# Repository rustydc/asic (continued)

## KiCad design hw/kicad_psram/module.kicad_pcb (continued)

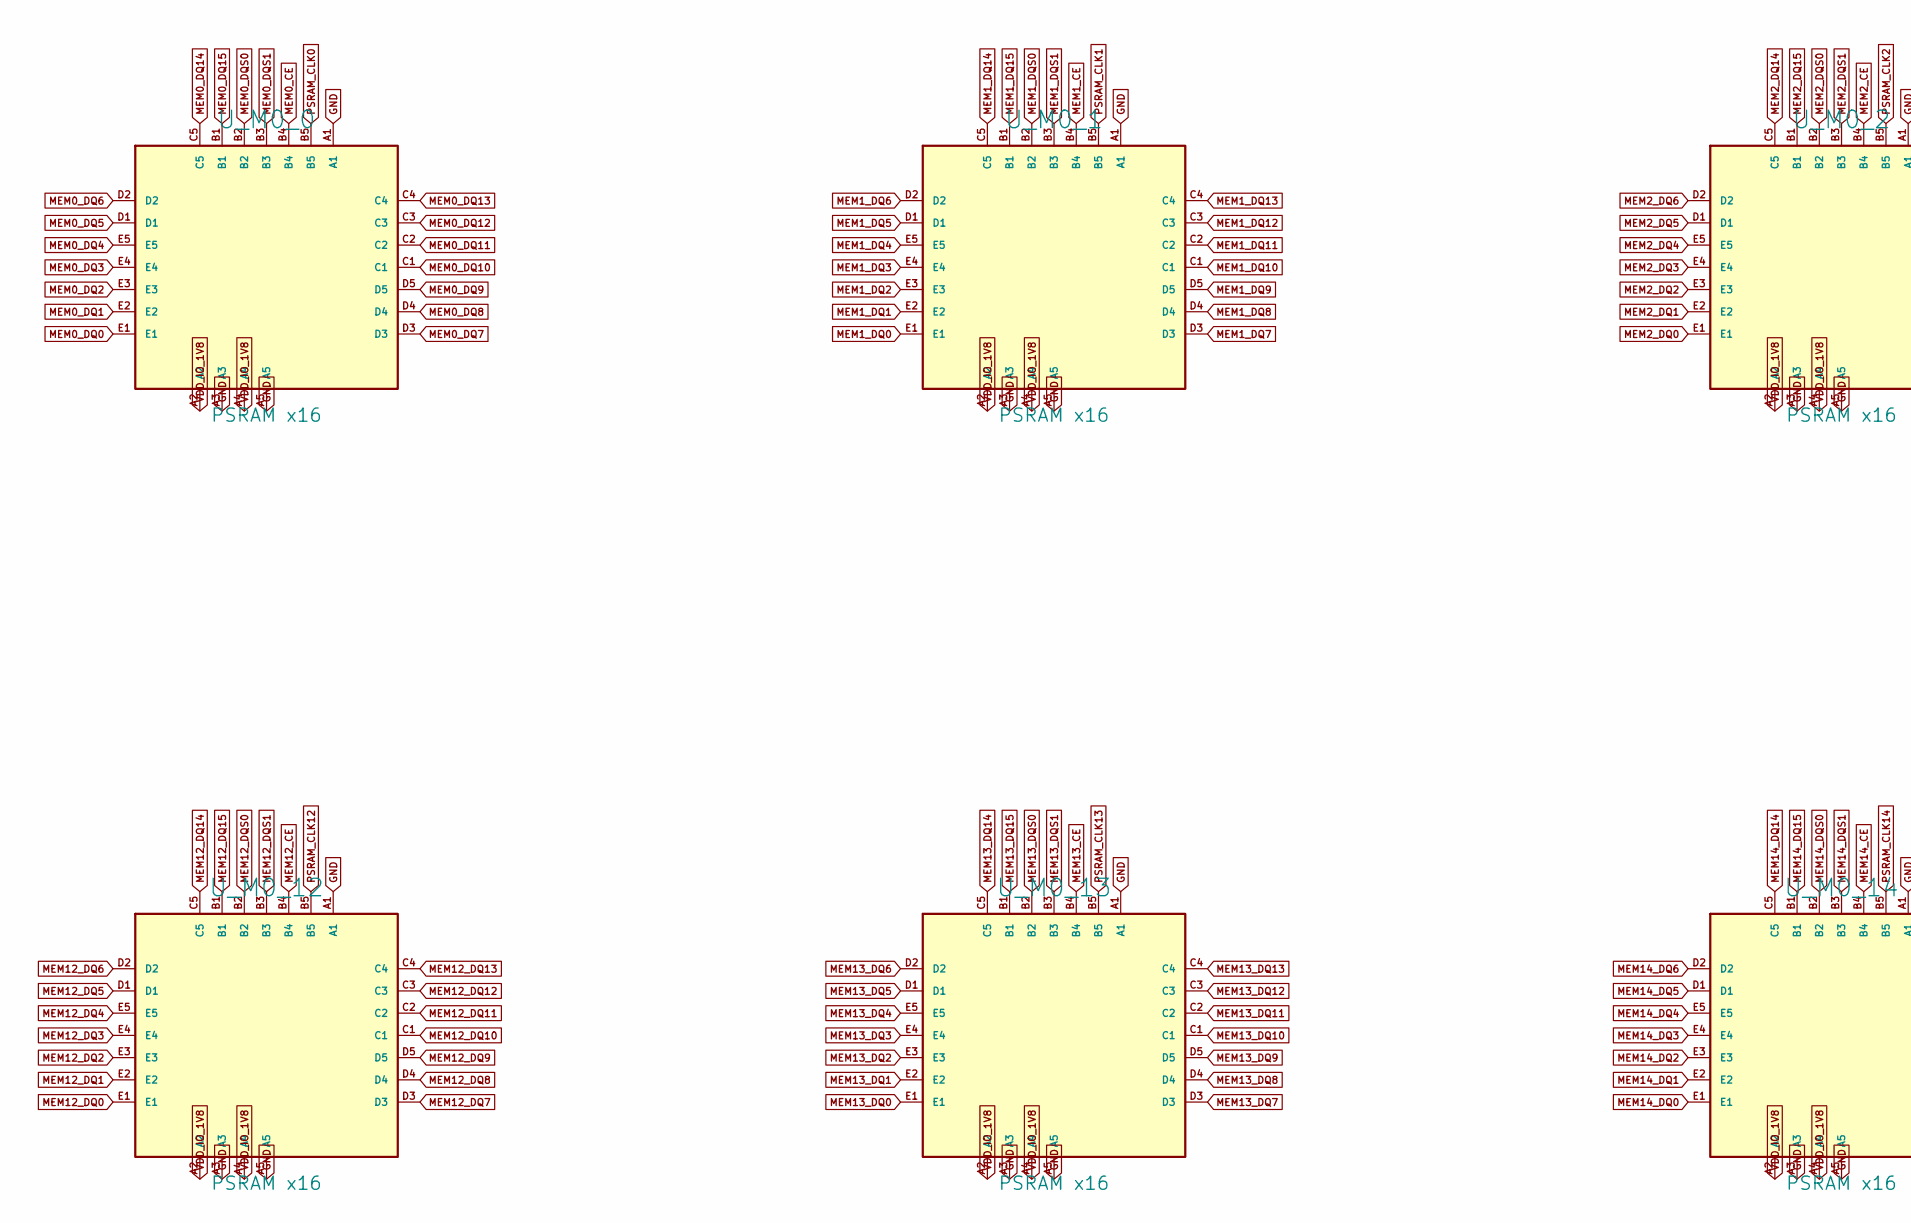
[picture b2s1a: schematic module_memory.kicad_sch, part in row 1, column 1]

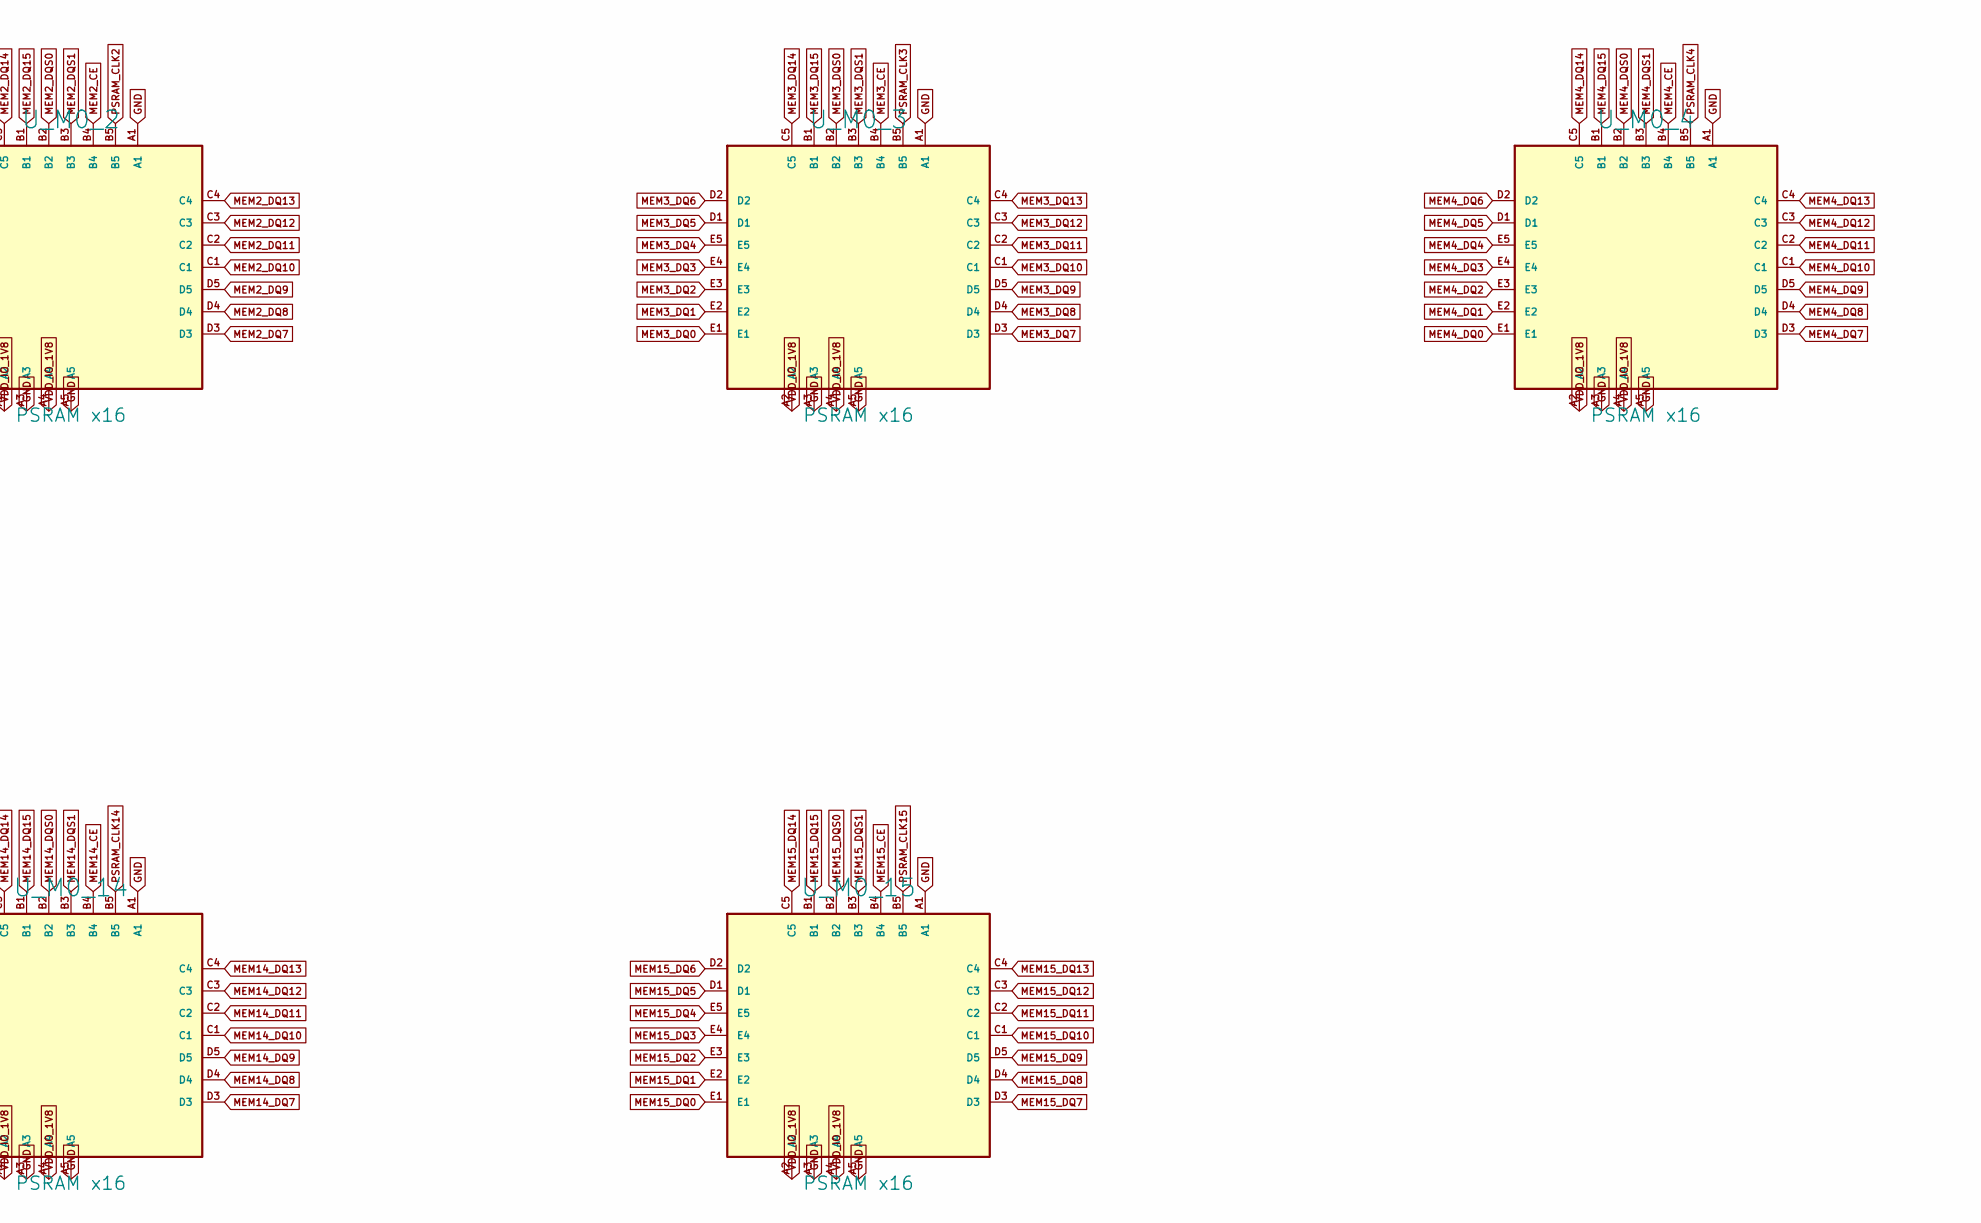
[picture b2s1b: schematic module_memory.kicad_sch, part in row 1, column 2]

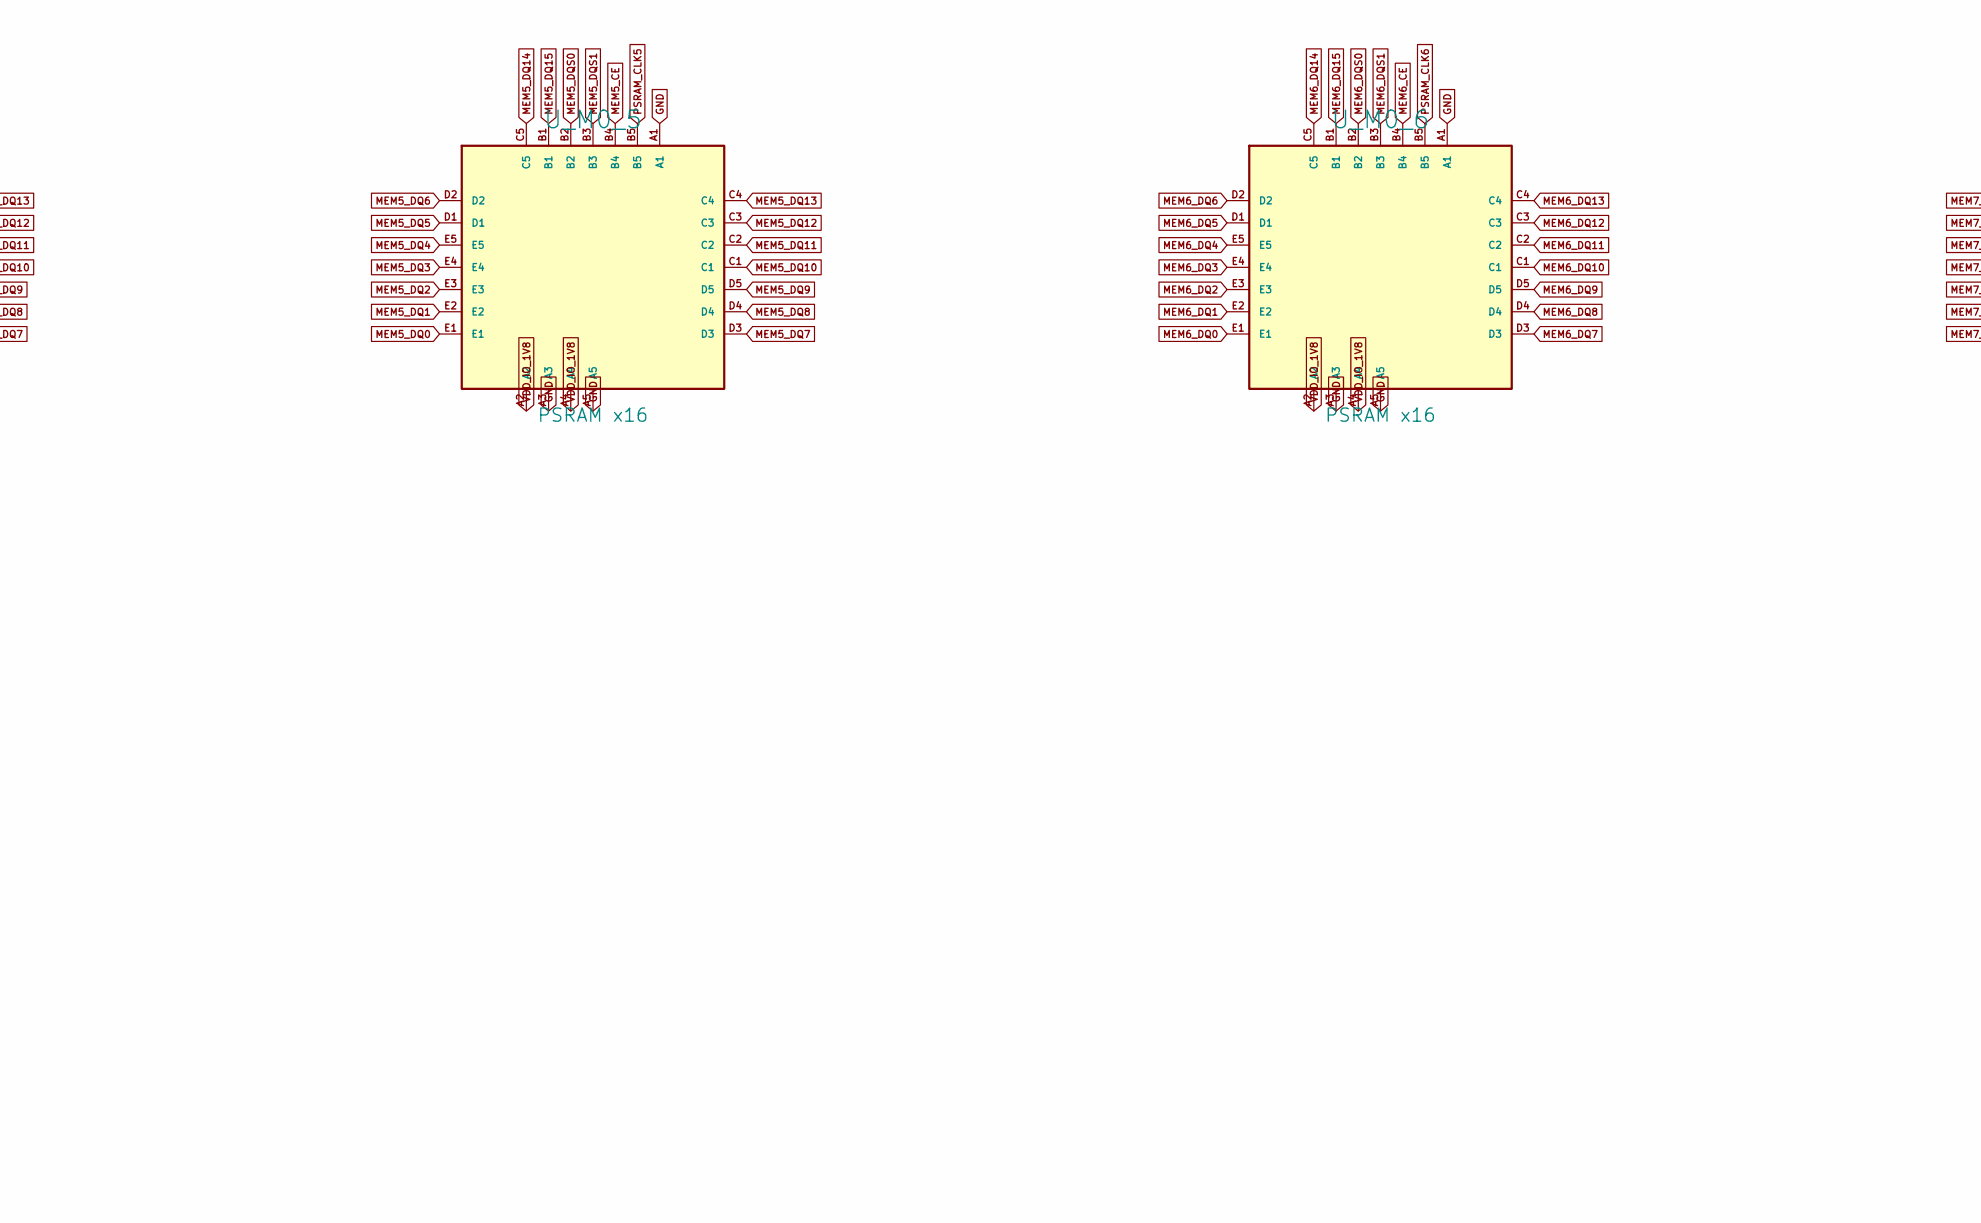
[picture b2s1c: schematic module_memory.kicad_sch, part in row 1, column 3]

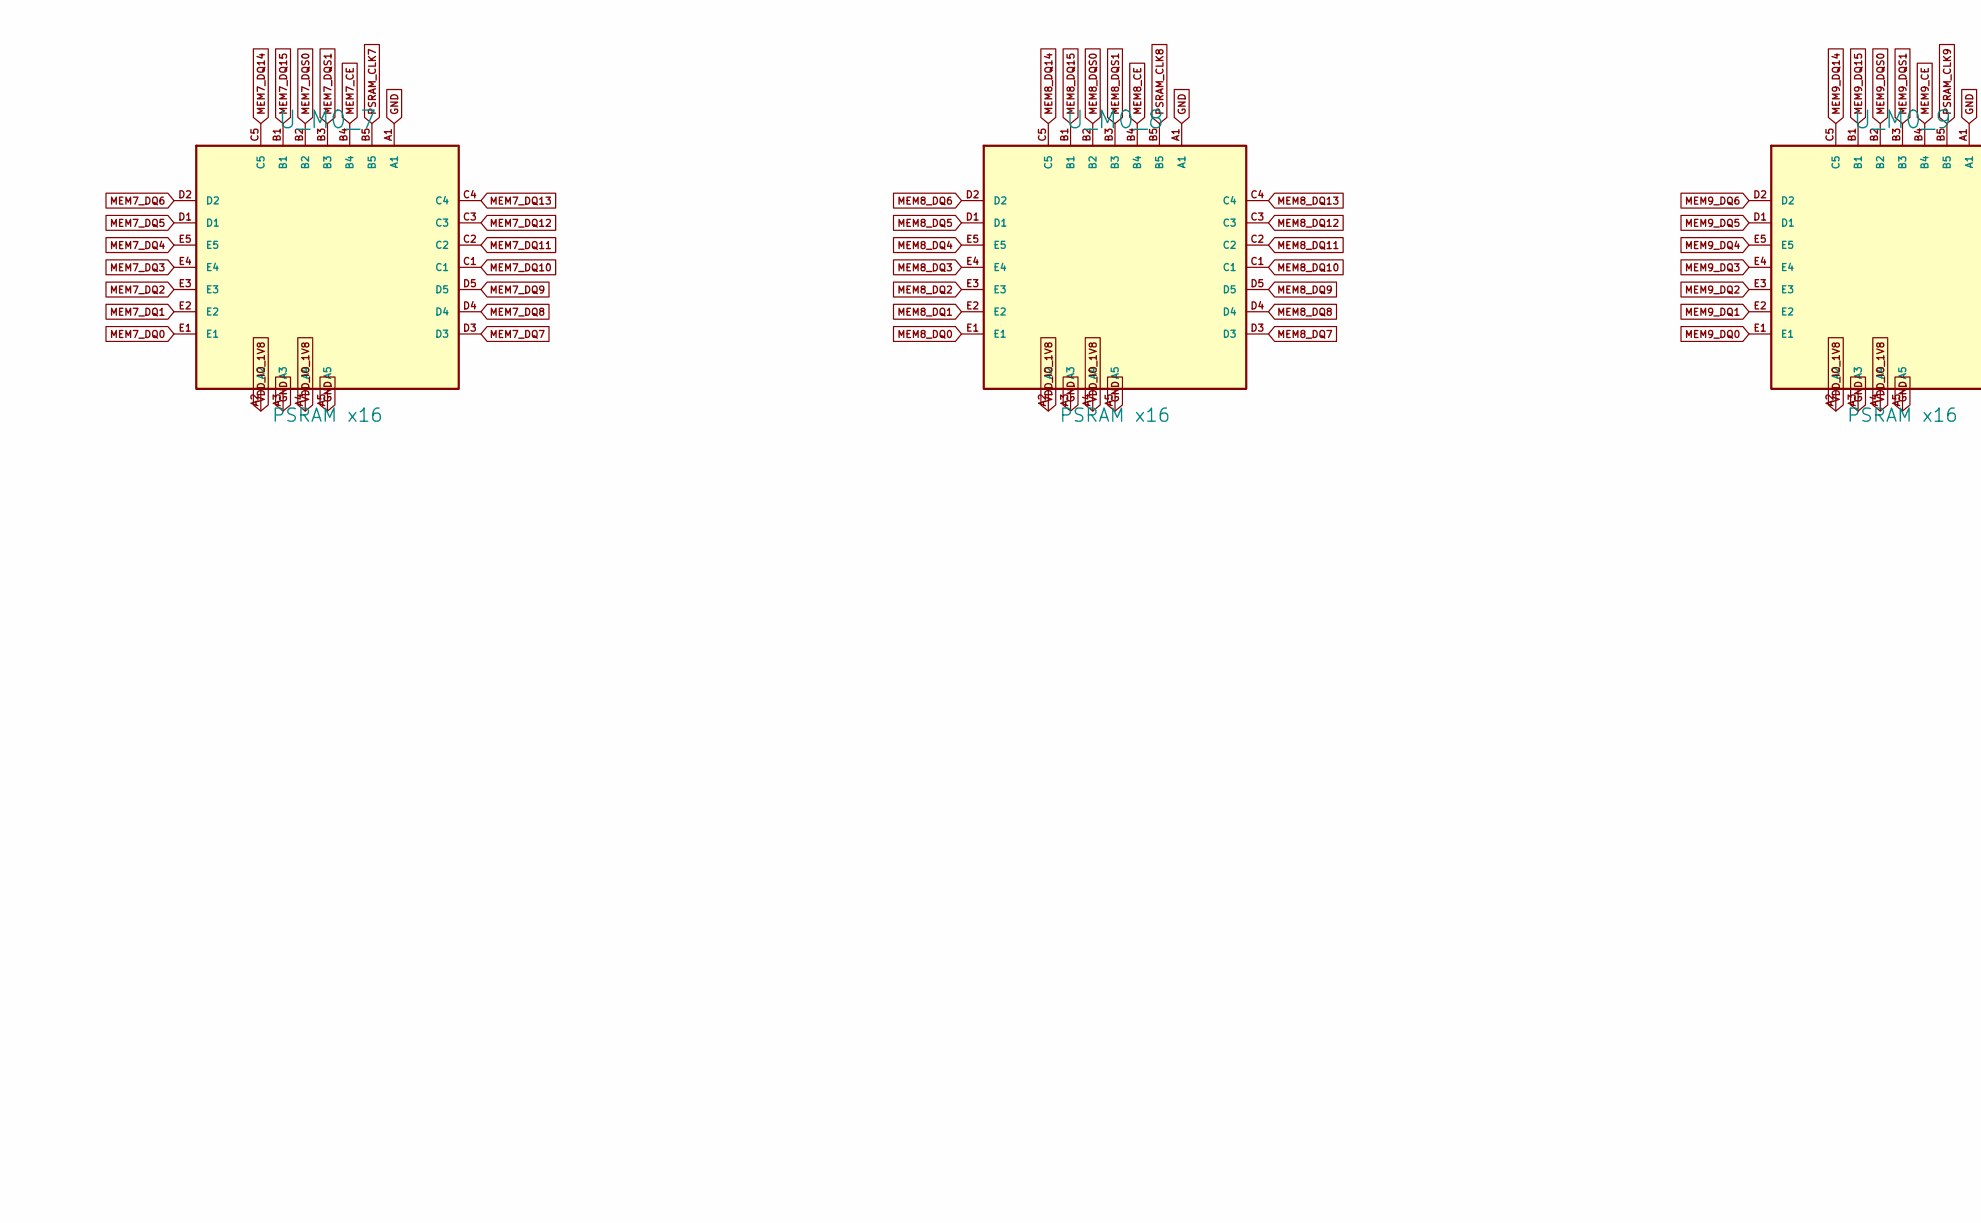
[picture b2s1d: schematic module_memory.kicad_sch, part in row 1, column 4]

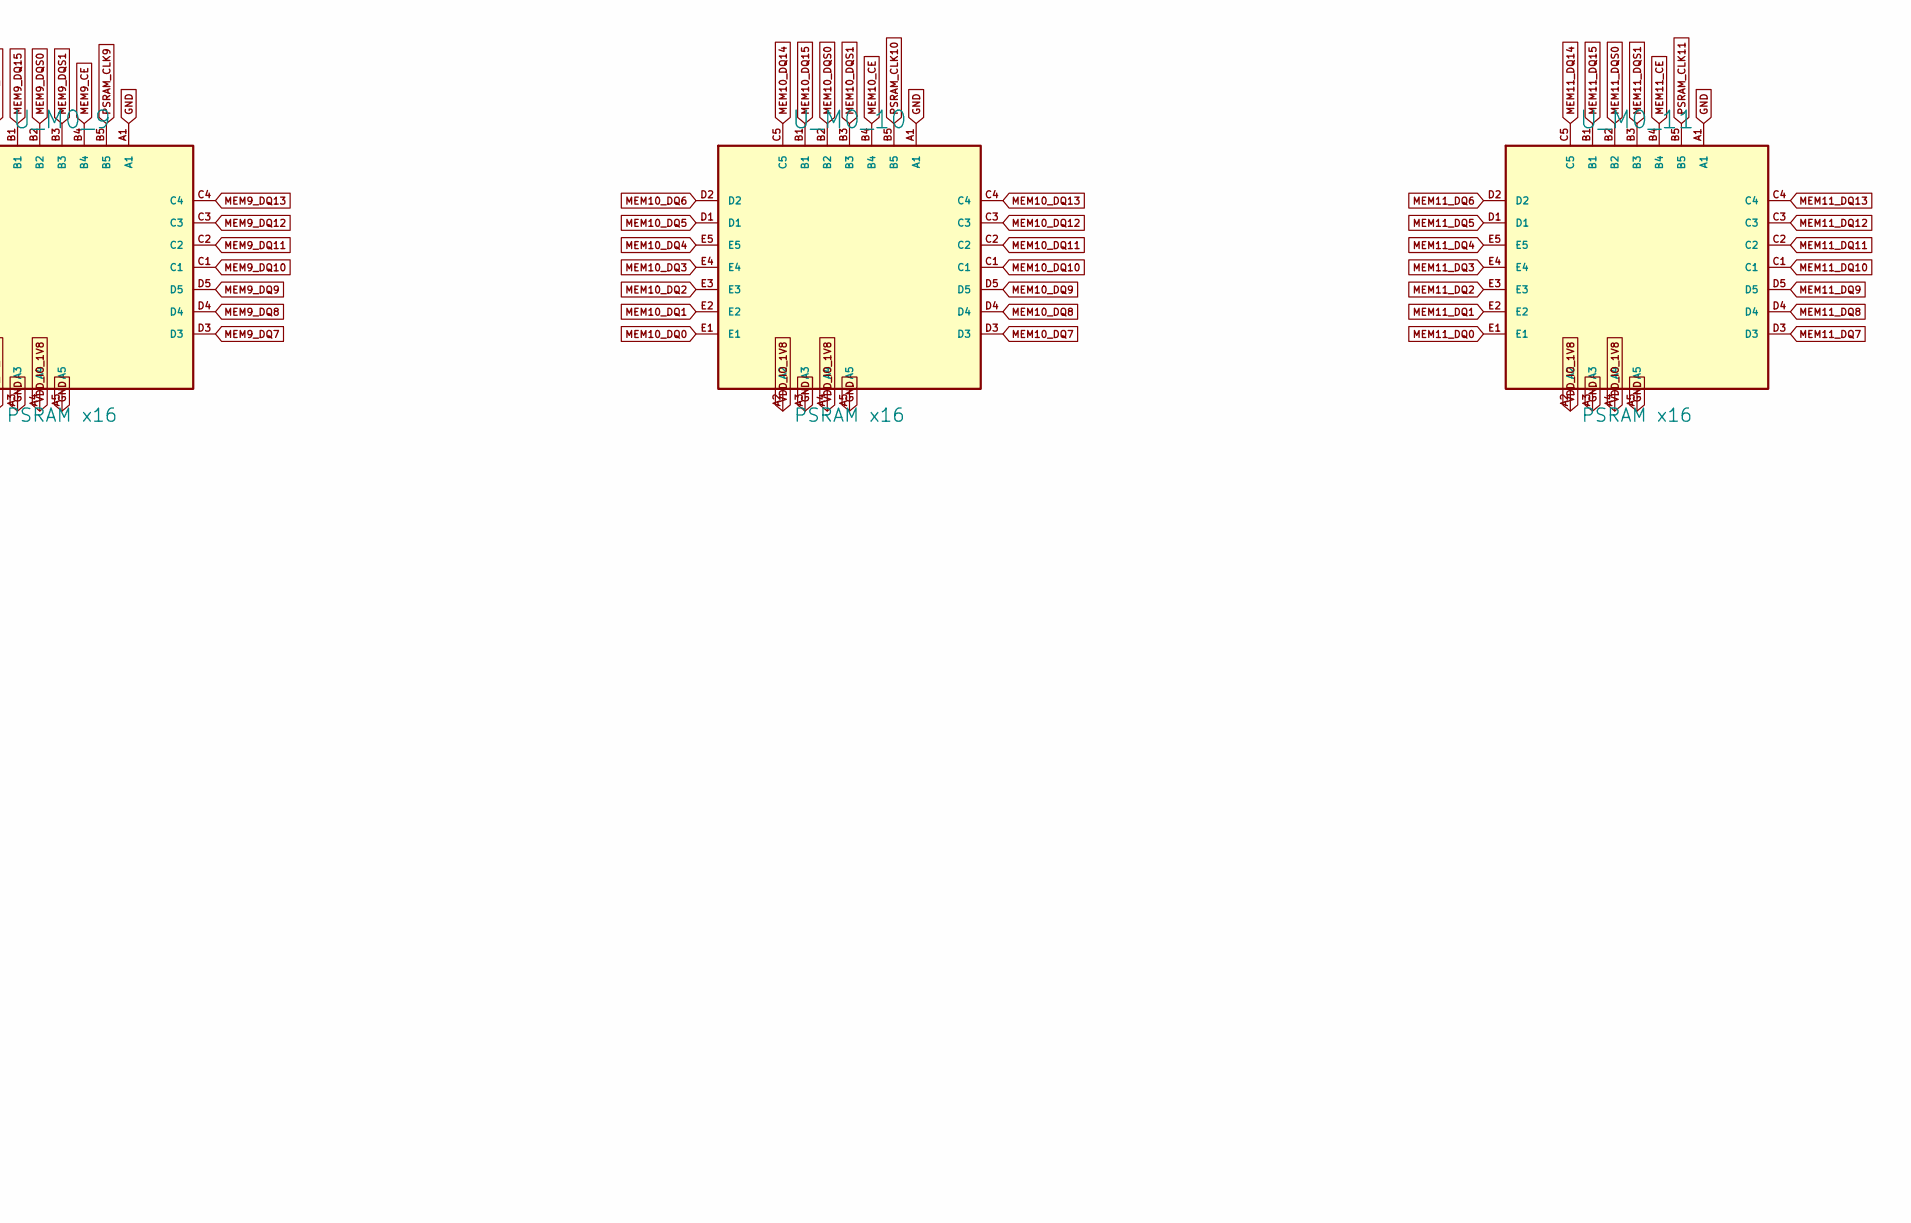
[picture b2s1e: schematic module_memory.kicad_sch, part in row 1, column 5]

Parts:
U_M0_0, U_M0_1, U_M0_2, U_M0_3, U_M0_4, U_M0_5, U_M0_6, U_M0_7, U_M0_8, U_M0_9, U_M0_10, U_M0_11, U_M0_12, U_M0_13, U_M0_14, U_M0_15: PSRAM x16; BGA24_5x5_P1.0

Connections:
GND: U_M0_0.A1, U_M0_0.A3, U_M0_0.A5, U_M0_1.A1, U_M0_1.A3, U_M0_1.A5, U_M0_2.A1, U_M0_2.A3, U_M0_2.A5, U_M0_3.A1, U_M0_3.A3, U_M0_3.A5, U_M0_4.A1, U_M0_4.A3, U_M0_4.A5, U_M0_5.A1, U_M0_5.A3, U_M0_5.A5, U_M0_6.A1, U_M0_6.A3, U_M0_6.A5, U_M0_7.A1, U_M0_7.A3, U_M0_7.A5, U_M0_8.A1, U_M0_8.A3, U_M0_8.A5, U_M0_9.A1, U_M0_9.A3, U_M0_9.A5, U_M0_10.A1, U_M0_10.A3, U_M0_10.A5, U_M0_11.A1, U_M0_11.A3, U_M0_11.A5, U_M0_12.A1, U_M0_12.A3, U_M0_12.A5, U_M0_13.A1, U_M0_13.A3, U_M0_13.A5, U_M0_14.A1, U_M0_14.A3, U_M0_14.A5, U_M0_15.A1, U_M0_15.A3, U_M0_15.A5; also elsewhere on the board
MEM0_CE: U_M0_0.B4
MEM0_DQ0: U_M0_0.E1
MEM0_DQ1: U_M0_0.E2
MEM0_DQ2: U_M0_0.E3
MEM0_DQ3: U_M0_0.E4
MEM0_DQ4: U_M0_0.E5
MEM0_DQ5: U_M0_0.D1
MEM0_DQ6: U_M0_0.D2
MEM0_DQ7: U_M0_0.D3
MEM0_DQ8: U_M0_0.D4
MEM0_DQ9: U_M0_0.D5
MEM0_DQ10: U_M0_0.C1
MEM0_DQ11: U_M0_0.C2
MEM0_DQ12: U_M0_0.C3
MEM0_DQ13: U_M0_0.C4
MEM0_DQ14: U_M0_0.C5
MEM0_DQ15: U_M0_0.B1
MEM0_DQS0: U_M0_0.B2
MEM0_DQS1: U_M0_0.B3
MEM1_CE: U_M0_1.B4
MEM1_DQ0: U_M0_1.E1
MEM1_DQ1: U_M0_1.E2
MEM1_DQ2: U_M0_1.E3
MEM1_DQ3: U_M0_1.E4
MEM1_DQ4: U_M0_1.E5
MEM1_DQ5: U_M0_1.D1
MEM1_DQ6: U_M0_1.D2
MEM1_DQ7: U_M0_1.D3
MEM1_DQ8: U_M0_1.D4
MEM1_DQ9: U_M0_1.D5
MEM1_DQ10: U_M0_1.C1
MEM1_DQ11: U_M0_1.C2
MEM1_DQ12: U_M0_1.C3
MEM1_DQ13: U_M0_1.C4
MEM1_DQ14: U_M0_1.C5
MEM1_DQ15: U_M0_1.B1
MEM1_DQS0: U_M0_1.B2
MEM1_DQS1: U_M0_1.B3
MEM2_CE: U_M0_2.B4
MEM2_DQ0: U_M0_2.E1
MEM2_DQ1: U_M0_2.E2
MEM2_DQ2: U_M0_2.E3
MEM2_DQ3: U_M0_2.E4
MEM2_DQ4: U_M0_2.E5
MEM2_DQ5: U_M0_2.D1
MEM2_DQ6: U_M0_2.D2
MEM2_DQ7: U_M0_2.D3
MEM2_DQ8: U_M0_2.D4
MEM2_DQ9: U_M0_2.D5
MEM2_DQ10: U_M0_2.C1
MEM2_DQ11: U_M0_2.C2
MEM2_DQ12: U_M0_2.C3
MEM2_DQ13: U_M0_2.C4
MEM2_DQ14: U_M0_2.C5
MEM2_DQ15: U_M0_2.B1
MEM2_DQS0: U_M0_2.B2
MEM2_DQS1: U_M0_2.B3
MEM3_CE: U_M0_3.B4
MEM3_DQ0: U_M0_3.E1
MEM3_DQ1: U_M0_3.E2
MEM3_DQ2: U_M0_3.E3
MEM3_DQ3: U_M0_3.E4
MEM3_DQ4: U_M0_3.E5
MEM3_DQ5: U_M0_3.D1
MEM3_DQ6: U_M0_3.D2
MEM3_DQ7: U_M0_3.D3
MEM3_DQ8: U_M0_3.D4
MEM3_DQ9: U_M0_3.D5
MEM3_DQ10: U_M0_3.C1
MEM3_DQ11: U_M0_3.C2
MEM3_DQ12: U_M0_3.C3
MEM3_DQ13: U_M0_3.C4
MEM3_DQ14: U_M0_3.C5
MEM3_DQ15: U_M0_3.B1
MEM3_DQS0: U_M0_3.B2
MEM3_DQS1: U_M0_3.B3
MEM4_CE: U_M0_4.B4
MEM4_DQ0: U_M0_4.E1
MEM4_DQ1: U_M0_4.E2
MEM4_DQ2: U_M0_4.E3
MEM4_DQ3: U_M0_4.E4
MEM4_DQ4: U_M0_4.E5
MEM4_DQ5: U_M0_4.D1
MEM4_DQ6: U_M0_4.D2
MEM4_DQ7: U_M0_4.D3
MEM4_DQ8: U_M0_4.D4
MEM4_DQ9: U_M0_4.D5
MEM4_DQ10: U_M0_4.C1
MEM4_DQ11: U_M0_4.C2
MEM4_DQ12: U_M0_4.C3
MEM4_DQ13: U_M0_4.C4
MEM4_DQ14: U_M0_4.C5
MEM4_DQ15: U_M0_4.B1
MEM4_DQS0: U_M0_4.B2
MEM4_DQS1: U_M0_4.B3
MEM5_CE: U_M0_5.B4
MEM5_DQ0: U_M0_5.E1
MEM5_DQ1: U_M0_5.E2
MEM5_DQ2: U_M0_5.E3
MEM5_DQ3: U_M0_5.E4
MEM5_DQ4: U_M0_5.E5
MEM5_DQ5: U_M0_5.D1
MEM5_DQ6: U_M0_5.D2
MEM5_DQ7: U_M0_5.D3
MEM5_DQ8: U_M0_5.D4
MEM5_DQ9: U_M0_5.D5
MEM5_DQ10: U_M0_5.C1
MEM5_DQ11: U_M0_5.C2
MEM5_DQ12: U_M0_5.C3
MEM5_DQ13: U_M0_5.C4
MEM5_DQ14: U_M0_5.C5
MEM5_DQ15: U_M0_5.B1
MEM5_DQS0: U_M0_5.B2
MEM5_DQS1: U_M0_5.B3
MEM6_CE: U_M0_6.B4
MEM6_DQ0: U_M0_6.E1
MEM6_DQ1: U_M0_6.E2
MEM6_DQ2: U_M0_6.E3
MEM6_DQ3: U_M0_6.E4
MEM6_DQ4: U_M0_6.E5
MEM6_DQ5: U_M0_6.D1
MEM6_DQ6: U_M0_6.D2
MEM6_DQ7: U_M0_6.D3
MEM6_DQ8: U_M0_6.D4
MEM6_DQ9: U_M0_6.D5
MEM6_DQ10: U_M0_6.C1
MEM6_DQ11: U_M0_6.C2
MEM6_DQ12: U_M0_6.C3
MEM6_DQ13: U_M0_6.C4
MEM6_DQ14: U_M0_6.C5
MEM6_DQ15: U_M0_6.B1
MEM6_DQS0: U_M0_6.B2
MEM6_DQS1: U_M0_6.B3
MEM7_CE: U_M0_7.B4
MEM7_DQ0: U_M0_7.E1
MEM7_DQ1: U_M0_7.E2
MEM7_DQ2: U_M0_7.E3
MEM7_DQ3: U_M0_7.E4
MEM7_DQ4: U_M0_7.E5
MEM7_DQ5: U_M0_7.D1
MEM7_DQ6: U_M0_7.D2
MEM7_DQ7: U_M0_7.D3
MEM7_DQ8: U_M0_7.D4
MEM7_DQ9: U_M0_7.D5
MEM7_DQ10: U_M0_7.C1
MEM7_DQ11: U_M0_7.C2
MEM7_DQ12: U_M0_7.C3
MEM7_DQ13: U_M0_7.C4
MEM7_DQ14: U_M0_7.C5
MEM7_DQ15: U_M0_7.B1
MEM7_DQS0: U_M0_7.B2
MEM7_DQS1: U_M0_7.B3
MEM8_CE: U_M0_8.B4
MEM8_DQ0: U_M0_8.E1
MEM8_DQ1: U_M0_8.E2
MEM8_DQ2: U_M0_8.E3
MEM8_DQ3: U_M0_8.E4
MEM8_DQ4: U_M0_8.E5
MEM8_DQ5: U_M0_8.D1
MEM8_DQ6: U_M0_8.D2
MEM8_DQ7: U_M0_8.D3
MEM8_DQ8: U_M0_8.D4
MEM8_DQ9: U_M0_8.D5
MEM8_DQ10: U_M0_8.C1
MEM8_DQ11: U_M0_8.C2
MEM8_DQ12: U_M0_8.C3
MEM8_DQ13: U_M0_8.C4
MEM8_DQ14: U_M0_8.C5
MEM8_DQ15: U_M0_8.B1
MEM8_DQS0: U_M0_8.B2
MEM8_DQS1: U_M0_8.B3
MEM9_CE: U_M0_9.B4
MEM9_DQ0: U_M0_9.E1
MEM9_DQ1: U_M0_9.E2
MEM9_DQ2: U_M0_9.E3
MEM9_DQ3: U_M0_9.E4
MEM9_DQ4: U_M0_9.E5
MEM9_DQ5: U_M0_9.D1
MEM9_DQ6: U_M0_9.D2
MEM9_DQ7: U_M0_9.D3
MEM9_DQ8: U_M0_9.D4
MEM9_DQ9: U_M0_9.D5
MEM9_DQ10: U_M0_9.C1
MEM9_DQ11: U_M0_9.C2
MEM9_DQ12: U_M0_9.C3
MEM9_DQ13: U_M0_9.C4
MEM9_DQ14: U_M0_9.C5
MEM9_DQ15: U_M0_9.B1
MEM9_DQS0: U_M0_9.B2
MEM9_DQS1: U_M0_9.B3
MEM10_CE: U_M0_10.B4
MEM10_DQ0: U_M0_10.E1
MEM10_DQ1: U_M0_10.E2
MEM10_DQ2: U_M0_10.E3
MEM10_DQ3: U_M0_10.E4
MEM10_DQ4: U_M0_10.E5
MEM10_DQ5: U_M0_10.D1
MEM10_DQ6: U_M0_10.D2
MEM10_DQ7: U_M0_10.D3
MEM10_DQ8: U_M0_10.D4
MEM10_DQ9: U_M0_10.D5
MEM10_DQ10: U_M0_10.C1
MEM10_DQ11: U_M0_10.C2
MEM10_DQ12: U_M0_10.C3
MEM10_DQ13: U_M0_10.C4
MEM10_DQ14: U_M0_10.C5
MEM10_DQ15: U_M0_10.B1
MEM10_DQS0: U_M0_10.B2
MEM10_DQS1: U_M0_10.B3
MEM11_CE: U_M0_11.B4
MEM11_DQ0: U_M0_11.E1
MEM11_DQ1: U_M0_11.E2
MEM11_DQ2: U_M0_11.E3
MEM11_DQ3: U_M0_11.E4
MEM11_DQ4: U_M0_11.E5
MEM11_DQ5: U_M0_11.D1
MEM11_DQ6: U_M0_11.D2
MEM11_DQ7: U_M0_11.D3
MEM11_DQ8: U_M0_11.D4
MEM11_DQ9: U_M0_11.D5
MEM11_DQ10: U_M0_11.C1
MEM11_DQ11: U_M0_11.C2
MEM11_DQ12: U_M0_11.C3
MEM11_DQ13: U_M0_11.C4
MEM11_DQ14: U_M0_11.C5
MEM11_DQ15: U_M0_11.B1
MEM11_DQS0: U_M0_11.B2
MEM11_DQS1: U_M0_11.B3
MEM12_CE: U_M0_12.B4
MEM12_DQ0: U_M0_12.E1
MEM12_DQ1: U_M0_12.E2
MEM12_DQ2: U_M0_12.E3
MEM12_DQ3: U_M0_12.E4
MEM12_DQ4: U_M0_12.E5
MEM12_DQ5: U_M0_12.D1
MEM12_DQ6: U_M0_12.D2
MEM12_DQ7: U_M0_12.D3
MEM12_DQ8: U_M0_12.D4
MEM12_DQ9: U_M0_12.D5
MEM12_DQ10: U_M0_12.C1
MEM12_DQ11: U_M0_12.C2
MEM12_DQ12: U_M0_12.C3
MEM12_DQ13: U_M0_12.C4
MEM12_DQ14: U_M0_12.C5
MEM12_DQ15: U_M0_12.B1
MEM12_DQS0: U_M0_12.B2
MEM12_DQS1: U_M0_12.B3
MEM13_CE: U_M0_13.B4
MEM13_DQ0: U_M0_13.E1
MEM13_DQ1: U_M0_13.E2
MEM13_DQ2: U_M0_13.E3
MEM13_DQ3: U_M0_13.E4
MEM13_DQ4: U_M0_13.E5
MEM13_DQ5: U_M0_13.D1
MEM13_DQ6: U_M0_13.D2
MEM13_DQ7: U_M0_13.D3
MEM13_DQ8: U_M0_13.D4
MEM13_DQ9: U_M0_13.D5
MEM13_DQ10: U_M0_13.C1
MEM13_DQ11: U_M0_13.C2
MEM13_DQ12: U_M0_13.C3
MEM13_DQ13: U_M0_13.C4
MEM13_DQ14: U_M0_13.C5
MEM13_DQ15: U_M0_13.B1
MEM13_DQS0: U_M0_13.B2
MEM13_DQS1: U_M0_13.B3
MEM14_CE: U_M0_14.B4
MEM14_DQ0: U_M0_14.E1
MEM14_DQ1: U_M0_14.E2
MEM14_DQ2: U_M0_14.E3
MEM14_DQ3: U_M0_14.E4
MEM14_DQ4: U_M0_14.E5
MEM14_DQ5: U_M0_14.D1
MEM14_DQ6: U_M0_14.D2
MEM14_DQ7: U_M0_14.D3
MEM14_DQ8: U_M0_14.D4
MEM14_DQ9: U_M0_14.D5
MEM14_DQ10: U_M0_14.C1
MEM14_DQ11: U_M0_14.C2
MEM14_DQ12: U_M0_14.C3
MEM14_DQ13: U_M0_14.C4
MEM14_DQ14: U_M0_14.C5
MEM14_DQ15: U_M0_14.B1
MEM14_DQS0: U_M0_14.B2
MEM14_DQS1: U_M0_14.B3
MEM15_CE: U_M0_15.B4
MEM15_DQ0: U_M0_15.E1
MEM15_DQ1: U_M0_15.E2
MEM15_DQ2: U_M0_15.E3
MEM15_DQ3: U_M0_15.E4
MEM15_DQ4: U_M0_15.E5
MEM15_DQ5: U_M0_15.D1
MEM15_DQ6: U_M0_15.D2
MEM15_DQ7: U_M0_15.D3
MEM15_DQ8: U_M0_15.D4
MEM15_DQ9: U_M0_15.D5
MEM15_DQ10: U_M0_15.C1
MEM15_DQ11: U_M0_15.C2
MEM15_DQ12: U_M0_15.C3
MEM15_DQ13: U_M0_15.C4
MEM15_DQ14: U_M0_15.C5
MEM15_DQ15: U_M0_15.B1
MEM15_DQS0: U_M0_15.B2
MEM15_DQS1: U_M0_15.B3
PSRAM_CLK0: U_M0_0.B5; also elsewhere on the board
PSRAM_CLK1: U_M0_1.B5; also elsewhere on the board
PSRAM_CLK2: U_M0_2.B5; also elsewhere on the board
PSRAM_CLK3: U_M0_3.B5; also elsewhere on the board
PSRAM_CLK4: U_M0_4.B5; also elsewhere on the board
PSRAM_CLK5: U_M0_5.B5; also elsewhere on the board
PSRAM_CLK6: U_M0_6.B5; also elsewhere on the board
PSRAM_CLK7: U_M0_7.B5; also elsewhere on the board
PSRAM_CLK8: U_M0_8.B5; also elsewhere on the board
PSRAM_CLK9: U_M0_9.B5; also elsewhere on the board
PSRAM_CLK10: U_M0_10.B5; also elsewhere on the board
PSRAM_CLK11: U_M0_11.B5; also elsewhere on the board
PSRAM_CLK12: U_M0_12.B5; also elsewhere on the board
PSRAM_CLK13: U_M0_13.B5; also elsewhere on the board
PSRAM_CLK14: U_M0_14.B5; also elsewhere on the board
PSRAM_CLK15: U_M0_15.B5; also elsewhere on the board
VDD_IO_1V8: U_M0_0.A2, U_M0_0.A4, U_M0_1.A2, U_M0_1.A4, U_M0_2.A2, U_M0_2.A4, U_M0_3.A2, U_M0_3.A4, U_M0_4.A2, U_M0_4.A4, U_M0_5.A2, U_M0_5.A4, U_M0_6.A2, U_M0_6.A4, U_M0_7.A2, U_M0_7.A4, U_M0_8.A2, U_M0_8.A4, U_M0_9.A2, U_M0_9.A4, U_M0_10.A2, U_M0_10.A4, U_M0_11.A2, U_M0_11.A4, U_M0_12.A2, U_M0_12.A4, U_M0_13.A2, U_M0_13.A4, U_M0_14.A2, U_M0_14.A4, U_M0_15.A2, U_M0_15.A4; also elsewhere on the board

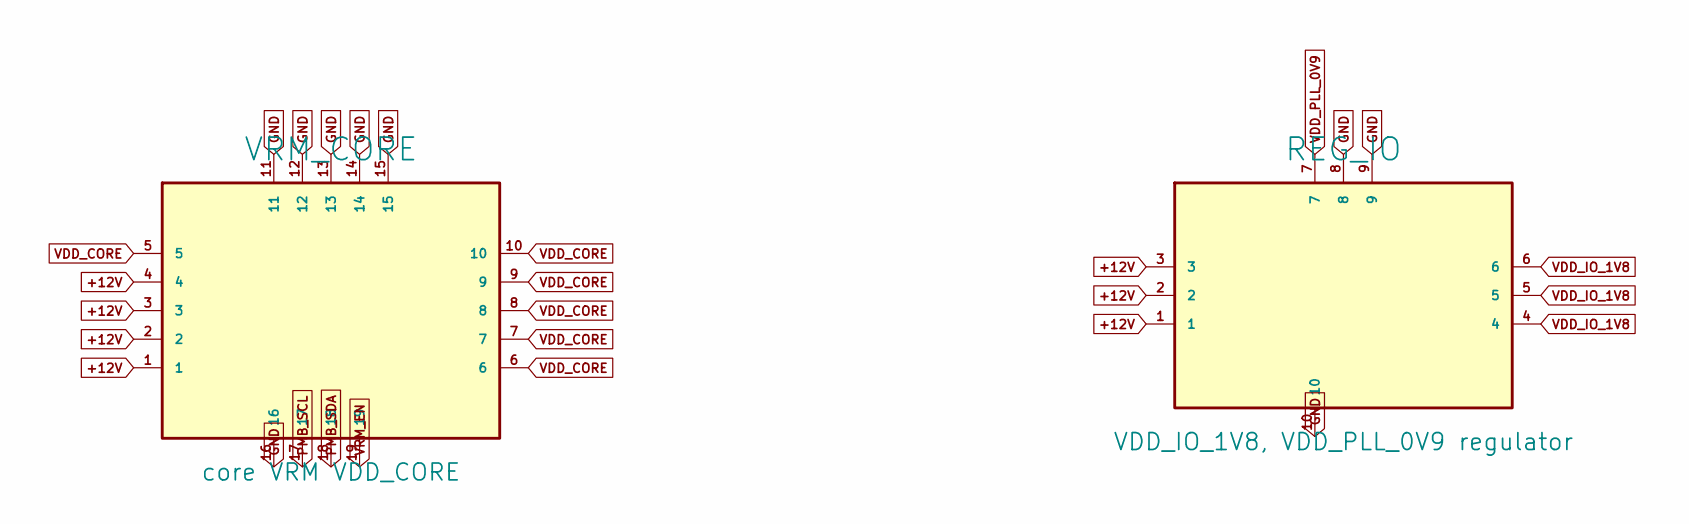
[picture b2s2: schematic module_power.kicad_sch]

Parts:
REG_IO: VDD_IO_1V8, VDD_PLL_0V9 regulator; REG_MODULE_20x6
VRM_CORE: core VRM VDD_CORE; VRM_MODULE_26x6

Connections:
+12V: REG_IO.1, REG_IO.2, REG_IO.3, VRM_CORE.1, VRM_CORE.2, VRM_CORE.3, VRM_CORE.4; also elsewhere on the board
GND: REG_IO.8, REG_IO.9, REG_IO.10, VRM_CORE.11, VRM_CORE.12, VRM_CORE.13, VRM_CORE.14, VRM_CORE.15, VRM_CORE.16; also elsewhere on the board
PMB_SCL: VRM_CORE.17; also elsewhere on the board
PMB_SDA: VRM_CORE.18; also elsewhere on the board
VDD_CORE: VRM_CORE.5, VRM_CORE.6, VRM_CORE.7, VRM_CORE.8, VRM_CORE.9, VRM_CORE.10; also elsewhere on the board
VDD_IO_1V8: REG_IO.4, REG_IO.5, REG_IO.6; also elsewhere on the board
VDD_PLL_0V9: REG_IO.7; also elsewhere on the board
VRM_EN: VRM_CORE.19; also elsewhere on the board

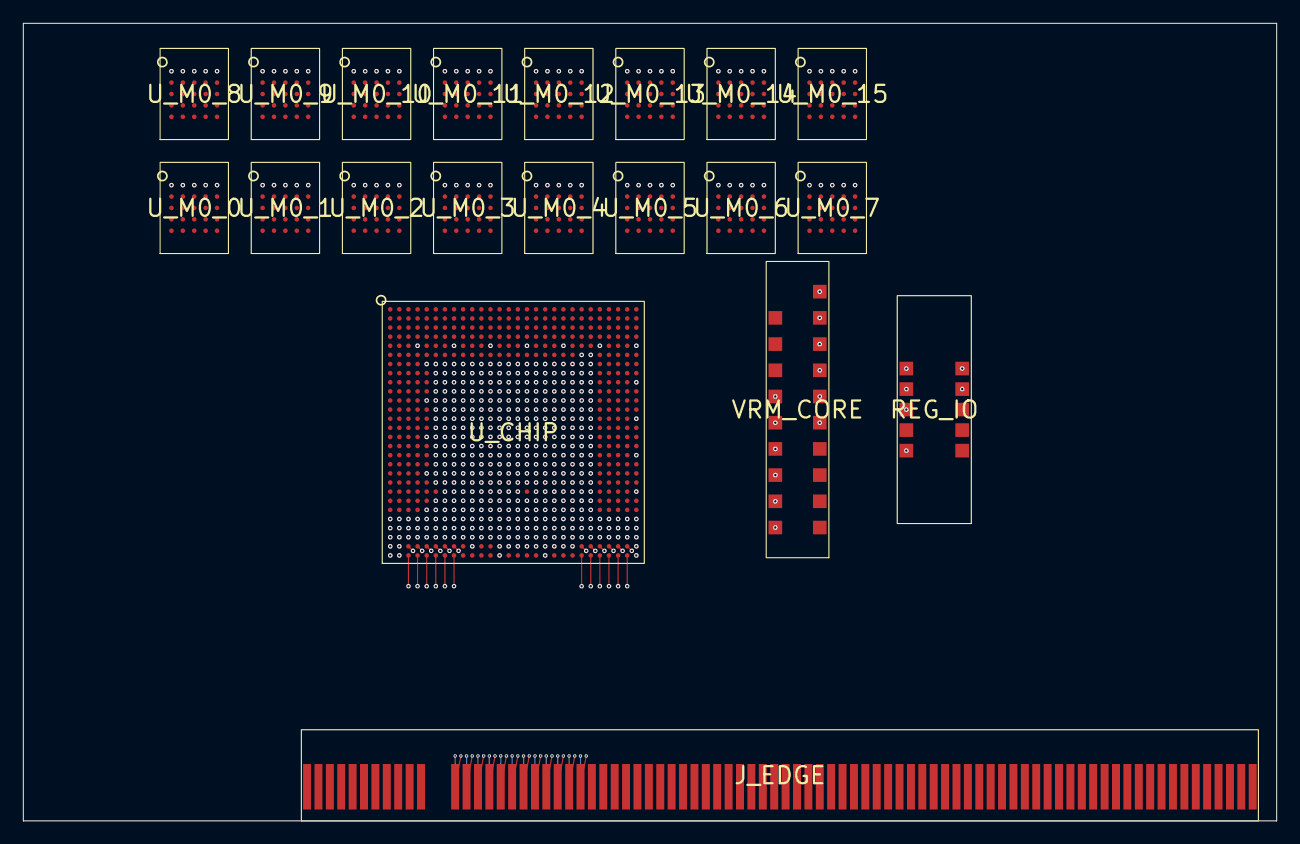
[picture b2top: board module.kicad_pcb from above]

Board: 8 copper layers, 110.0 x 70.0 mm, 20 parts (0 on the bottom side), 58 nets.
